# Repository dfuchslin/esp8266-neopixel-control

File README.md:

# ESP8266 Neopixel Control

Project setup inspired by https://github.com/tenderlove/esp8266aq (Thank you!)

https://www.electronics-lab.com/project/home-automation-using-nodemcu-esp8266-board/

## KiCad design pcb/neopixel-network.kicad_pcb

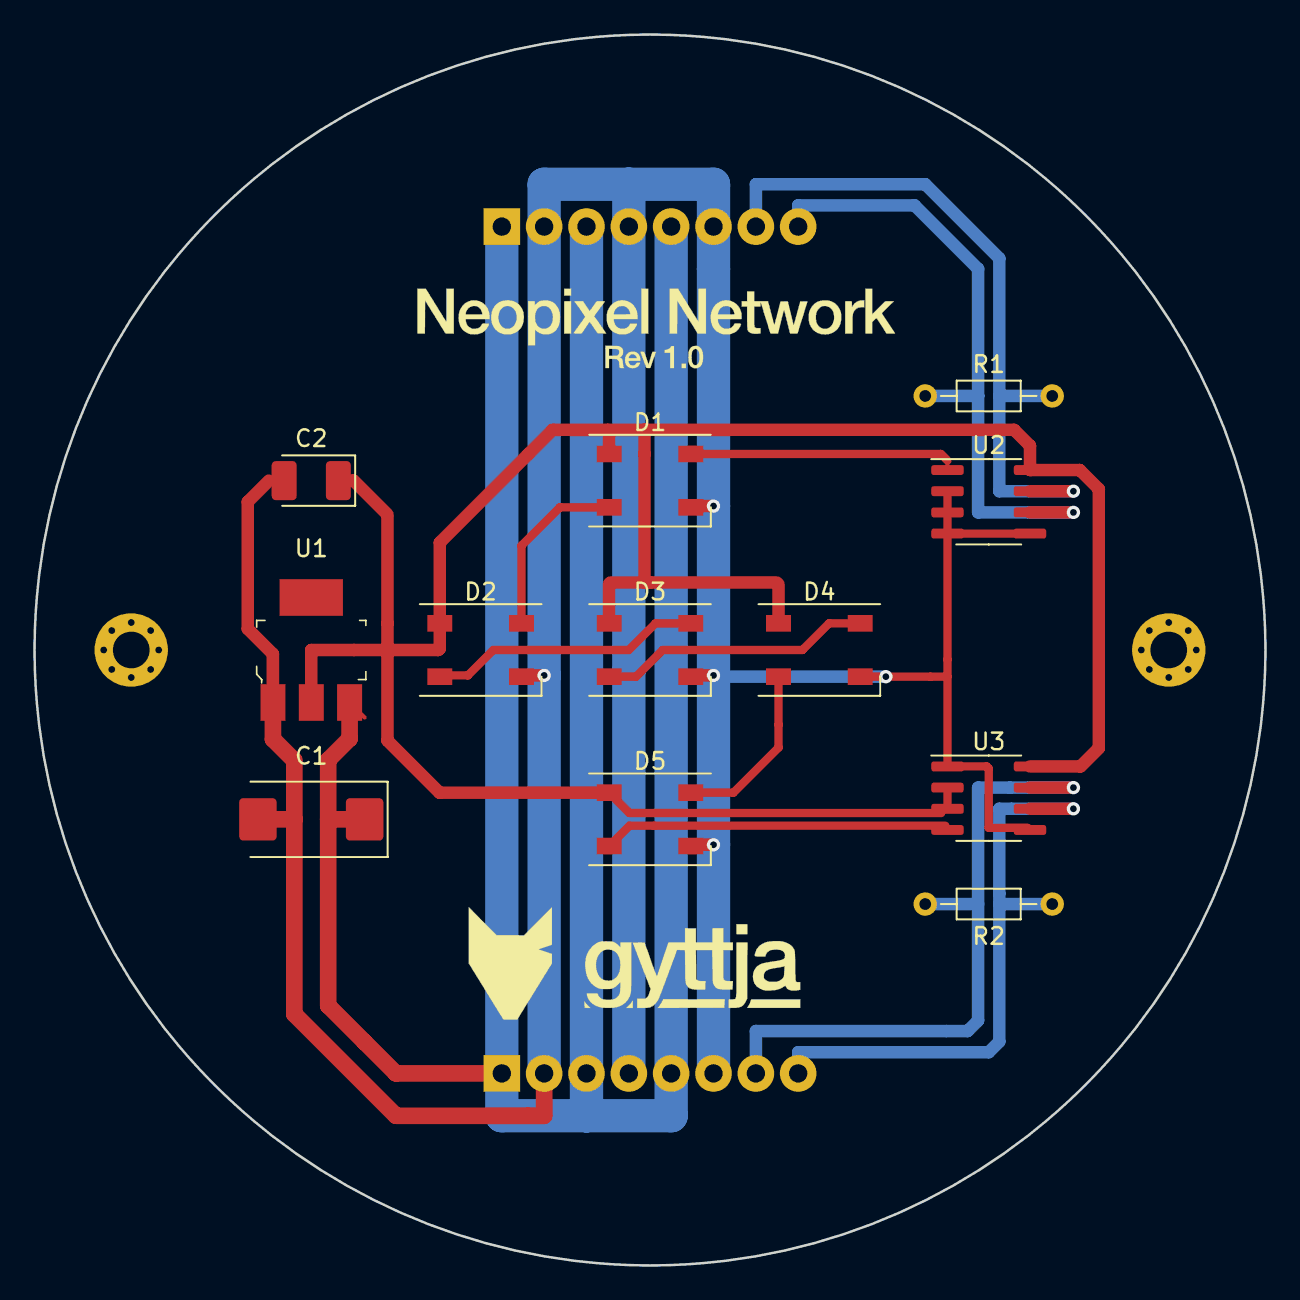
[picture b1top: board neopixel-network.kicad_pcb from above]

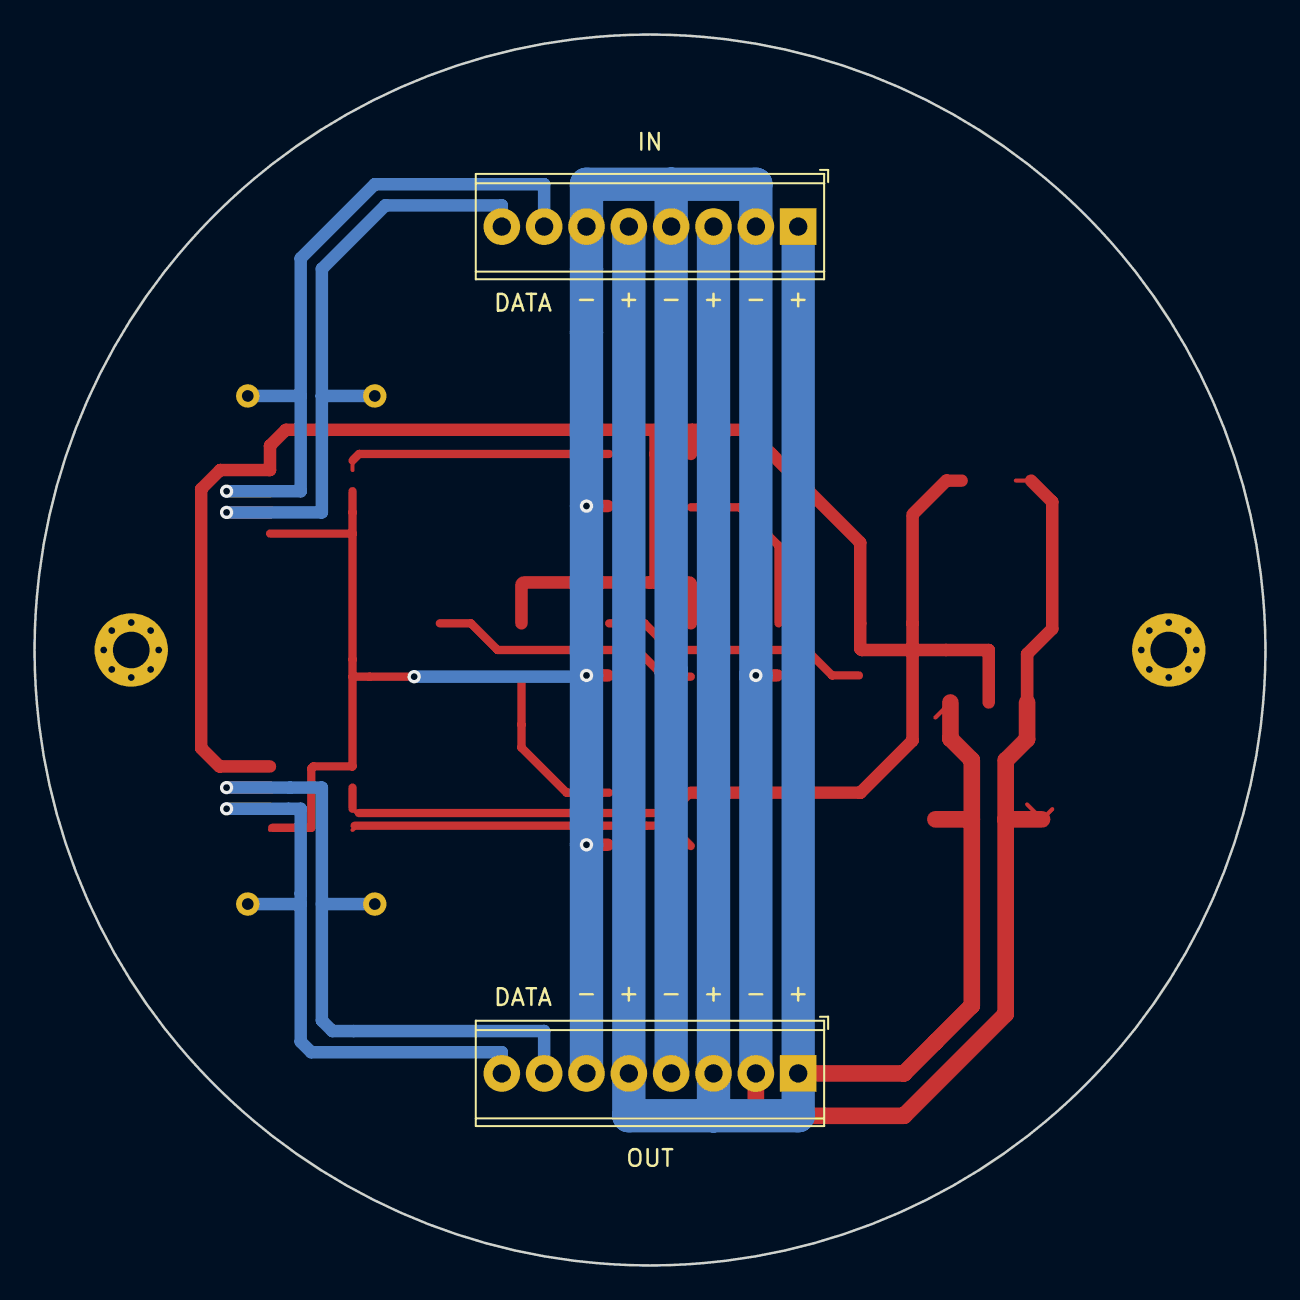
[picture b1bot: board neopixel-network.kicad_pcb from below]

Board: 2 copper layers, 73.8 x 73.8 mm, 14 parts (2 on the bottom side), 13 nets.

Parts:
C1: 100; CP_EIA-7343-31_Kemet-D_Pad2.25x2.55mm_HandSolder
C2: 10; CP_EIA-3528-21_Kemet-B_Pad1.50x2.35mm_HandSolder
D1, D2, D3, D4, D5: SK6812; LED_SK6812_PLCC4_5.0x5.0mm_P3.2mm
IN: Screw_Terminal_01x08; TerminalBlock_Phoenix_MPT-0,5-8-2.54_1x08_P2.54mm_Horizontal
OUT: Screw_Terminal_01x08; TerminalBlock_Phoenix_MPT-0,5-8-2.54_1x08_P2.54mm_Horizontal
R1, R2: 120; R_Axial_DIN0204_L3.6mm_D1.6mm_P7.62mm_Horizontal
U1: LD1117IS50; SOT-223
U2, U3: SN65176BDR; SOIC-8_3.9x4.9mm_P1.27mm

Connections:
12V: C1.1, IN.1, IN.3, IN.5, OUT.1, OUT.3, OUT.5, U1.3
unnamed: C1.2, C2.2, D1.1, D2.1, D3.1, D4.1, D5.1, IN.2, IN.4, IN.6, OUT.2, OUT.4, OUT.6, U1.1, U2.2, U2.3, U2.4, U2.5, U3.1, U3.5
unnamed: C2.1, D1.3, D2.3, D3.3, D4.3, D5.3, U1.2, U2.8, U3.2, U3.3, U3.8
unnamed: D1.2, U2.1
unnamed: D1.4, D2.2
unnamed: D2.4, D3.2
unnamed: D3.4, D4.2
unnamed: D4.4, D5.2
unnamed: D5.4, U3.4
unnamed: IN.7, R1.2, U2.7
unnamed: IN.8, R1.1, U2.6
unnamed: OUT.7, R2.2, U3.7
unnamed: OUT.8, R2.1, U3.6

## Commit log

2020-10-10 adding draft firmware, file setup
2020-10-10 clean up makefile
2020-10-11 add pcb
2020-11-05 fix bug where code actually did nothing...
2020-11-05 add updated pcb
2020-11-05 increase num leds to 3 lamps (15 leds)
2020-11-15 add relay
2020-12-05 Increase to 60 LEDs
2020-12-14 Add OTA update
2020-12-19 handle more state, hack to pause and allow stabilization
2021-05-02 Refresh status in loop to make sure all lamps are lit, remove delay hack
